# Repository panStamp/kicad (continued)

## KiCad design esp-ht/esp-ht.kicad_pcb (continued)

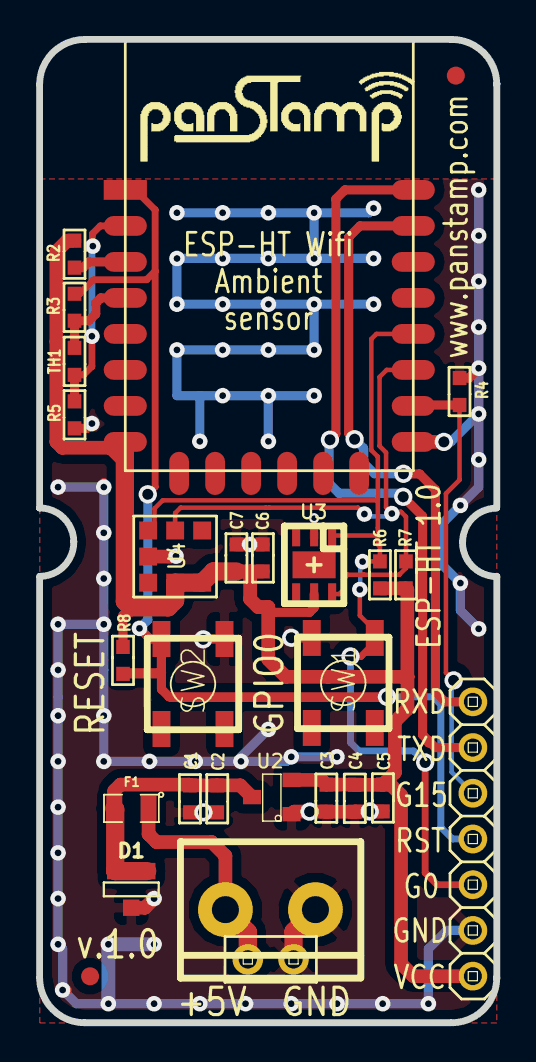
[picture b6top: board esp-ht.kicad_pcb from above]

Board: 2 copper layers, 25.4 x 54.6 mm, 28 parts (0 on the bottom side), 13 nets.

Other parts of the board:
fiducial: VAL**; fiducial
fiducial#2: VAL**; fiducial

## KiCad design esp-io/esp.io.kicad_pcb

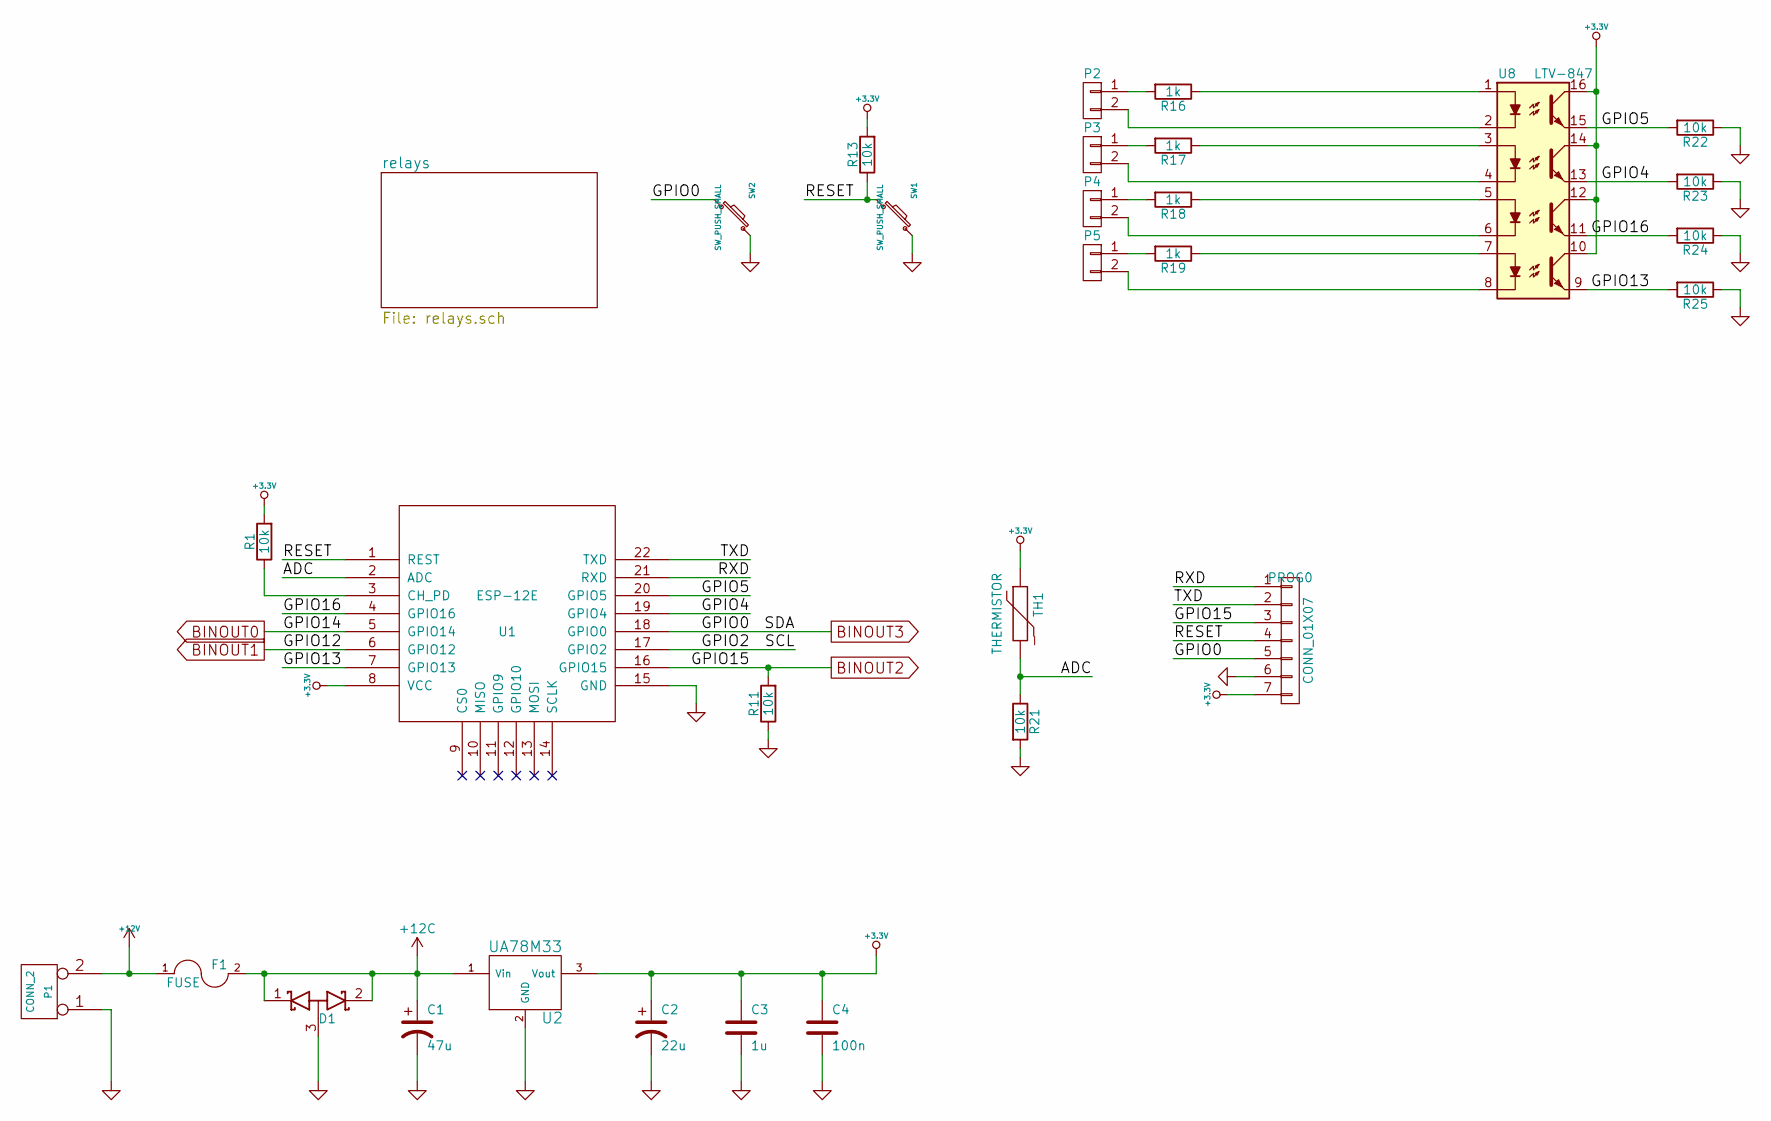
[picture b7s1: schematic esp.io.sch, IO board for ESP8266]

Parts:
C1: 47u; SMDCPOL_6.3
C2: 22u; SMDCPOL_5
C3: 1u; SM0603S
C4: 100n; SM0603S
D1: D_Schottky_x2_ACom_KKA; SOT23
F1: FUSE; SM1206
P1: CONN_2; terminal_block_5mm_2P
P2, P3, P4, P5: CONN_01X02; terminal_block_5mm_2P
PROG0: CONN_01X07; pinhead-1X07
R1, R11, R13, R21, R22, R23, R24, R25: 10k; SM0603S
R16, R17, R18, R19: 1k; SM0603S
SW1, SW2: SW_PUSH_SMALL; switch-tact-noah
TH1: THERMISTOR; SM0603S
U1: ESP-12E
U2: UA78M33; SOT223
U8: LTV-847; DIP16_SMD

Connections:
+3.3V: C2.1, C3.1, C4.1, PROG0.7, R1.2, R13.2, TH1.1, U1.8 (VCC), U2.3 (Vout), U8.10, U8.12, U8.14, U8.16
+12C: C1.1, D1.1 (K), D1.2 (K), F1.2, U2.1 (Vin); also elsewhere on the board
+12V: F1.1, P1.2 (PM)
/ADC: R21.1, TH1.2, U1.2 (ADC)
/GPIO2: U1.17 (GPIO2)
/GPIO4: R23.2, U1.19 (GPIO4), U8.13
/GPIO5: R22.2, U1.20 (GPIO5), U8.15
/GPIO13: R25.2, U1.7 (GPIO13), U8.9
/GPIO16: R24.2, U1.4 (GPIO16), U8.11
/RESET: PROG0.4, R13.1, SW1.2, U1.1 (REST)
/RXD: PROG0.1, U1.21 (RXD)
/TXD: PROG0.2, U1.22 (TXD)
BINOUT0: U1.5 (GPIO14); also elsewhere on the board
BINOUT1: U1.6 (GPIO12); also elsewhere on the board
BINOUT2: PROG0.3, R11.2, U1.16 (GPIO15); also elsewhere on the board
BINOUT3: PROG0.5, SW2.2, U1.18 (GPIO0); also elsewhere on the board
GND: C1.2, C2.2, C3.2, C4.2, D1.3 (A), P1.1, PROG0.6, R11.1, R21.2, R22.1, R23.1, R24.1, R25.1, SW1.1, SW2.1, U1.15 (GND), U2.2 (GND), U2.4; also elsewhere on the board
unnamed: P2.1, R16.2
unnamed: P2.2, U8.2
unnamed: P3.1, R17.2
unnamed: P3.2, U8.4
unnamed: P4.1, R18.2
unnamed: P4.2, U8.6
unnamed: P5.1, R19.2
unnamed: P5.2, U8.8
unnamed: R1.1, U1.3 (CH_PD)
unnamed: R16.1, U8.1
unnamed: R17.1, U8.3
unnamed: R18.1, U8.5
unnamed: R19.1, U8.7

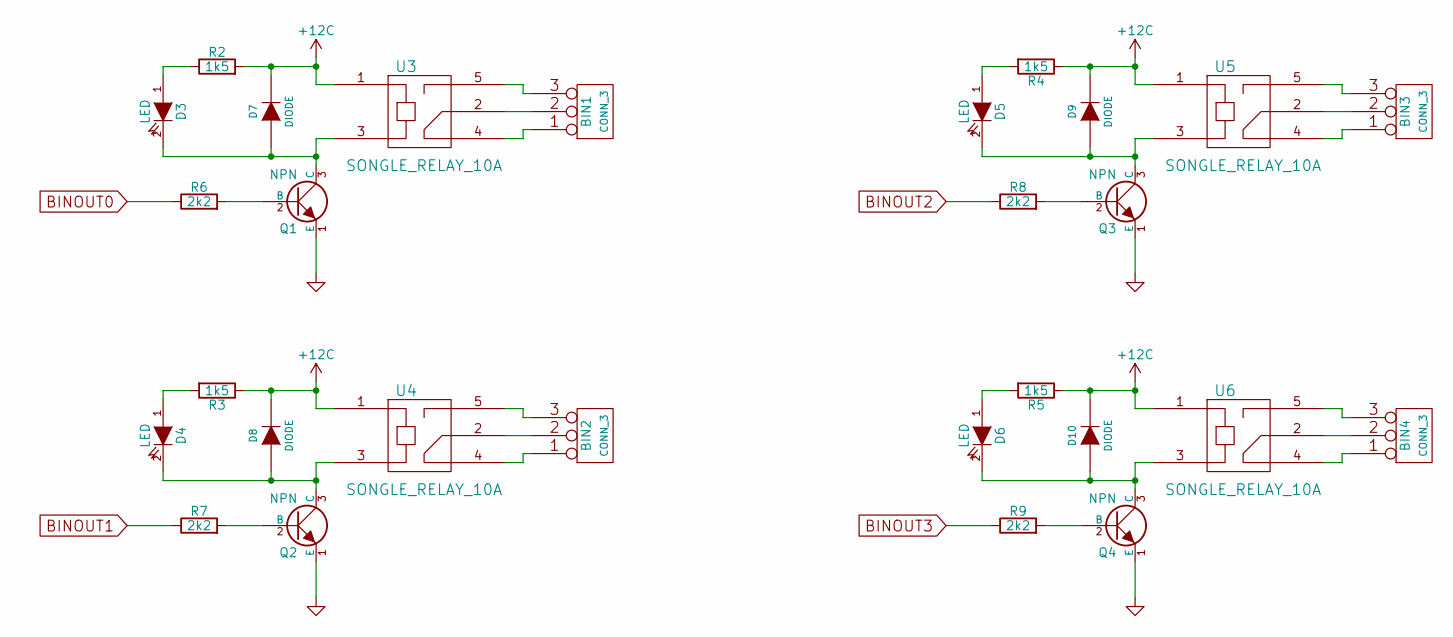
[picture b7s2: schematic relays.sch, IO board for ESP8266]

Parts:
BIN1, BIN2, BIN3, BIN4: CONN_3; terminal_block_5mm_3P
D3, D4, D5, D6: LED; SM0603S_POL
D7, D8, D9, D10: DIODE; SOD323
Q1, Q2, Q3, Q4: NPN; SOT23EBC
R2, R3, R4, R5: 1k5; SM0603S
R6, R7, R8, R9: 2k2; SM0603S
U3, U4, U5, U6: SONGLE_RELAY_10A

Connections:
+12C: D7.2 (K), D8.2 (K), D9.2 (K), D10.2 (K), R2.2, R3.1, R4.1, R5.1, U3.1, U4.1, U5.1, U6.1; also elsewhere on the board
BINOUT0: R6.1; also elsewhere on the board
BINOUT1: R7.1; also elsewhere on the board
BINOUT2: R8.1; also elsewhere on the board
BINOUT3: R9.1; also elsewhere on the board
GND: Q1.1 (E), Q2.1 (E), Q3.1 (E), Q4.1 (E); also elsewhere on the board
unnamed: BIN1.1, U3.4
unnamed: BIN1.2 (PM), U3.2
unnamed: BIN1.3, U3.5
unnamed: BIN2.1, U4.4
unnamed: BIN2.2 (PM), U4.2
unnamed: BIN2.3, U4.5
unnamed: BIN3.1, U5.4
unnamed: BIN3.2 (PM), U5.2
unnamed: BIN3.3, U5.5
unnamed: BIN4.1, U6.4
unnamed: BIN4.2 (PM), U6.2
unnamed: BIN4.3, U6.5
unnamed: D3.1 (A), R2.1
unnamed: D3.2 (K), D7.1 (A), Q1.3 (C), U3.3
unnamed: D4.1 (A), R3.2
unnamed: D4.2 (K), D8.1 (A), Q2.3 (C), U4.3
unnamed: D5.1 (A), R4.2
unnamed: D5.2 (K), D9.1 (A), Q3.3 (C), U5.3
unnamed: D6.1 (A), R5.2
unnamed: D6.2 (K), D10.1 (A), Q4.3 (C), U6.3
unnamed: Q1.2 (B), R6.2
unnamed: Q2.2 (B), R7.2
unnamed: Q3.2 (B), R8.2
unnamed: Q4.2 (B), R9.2

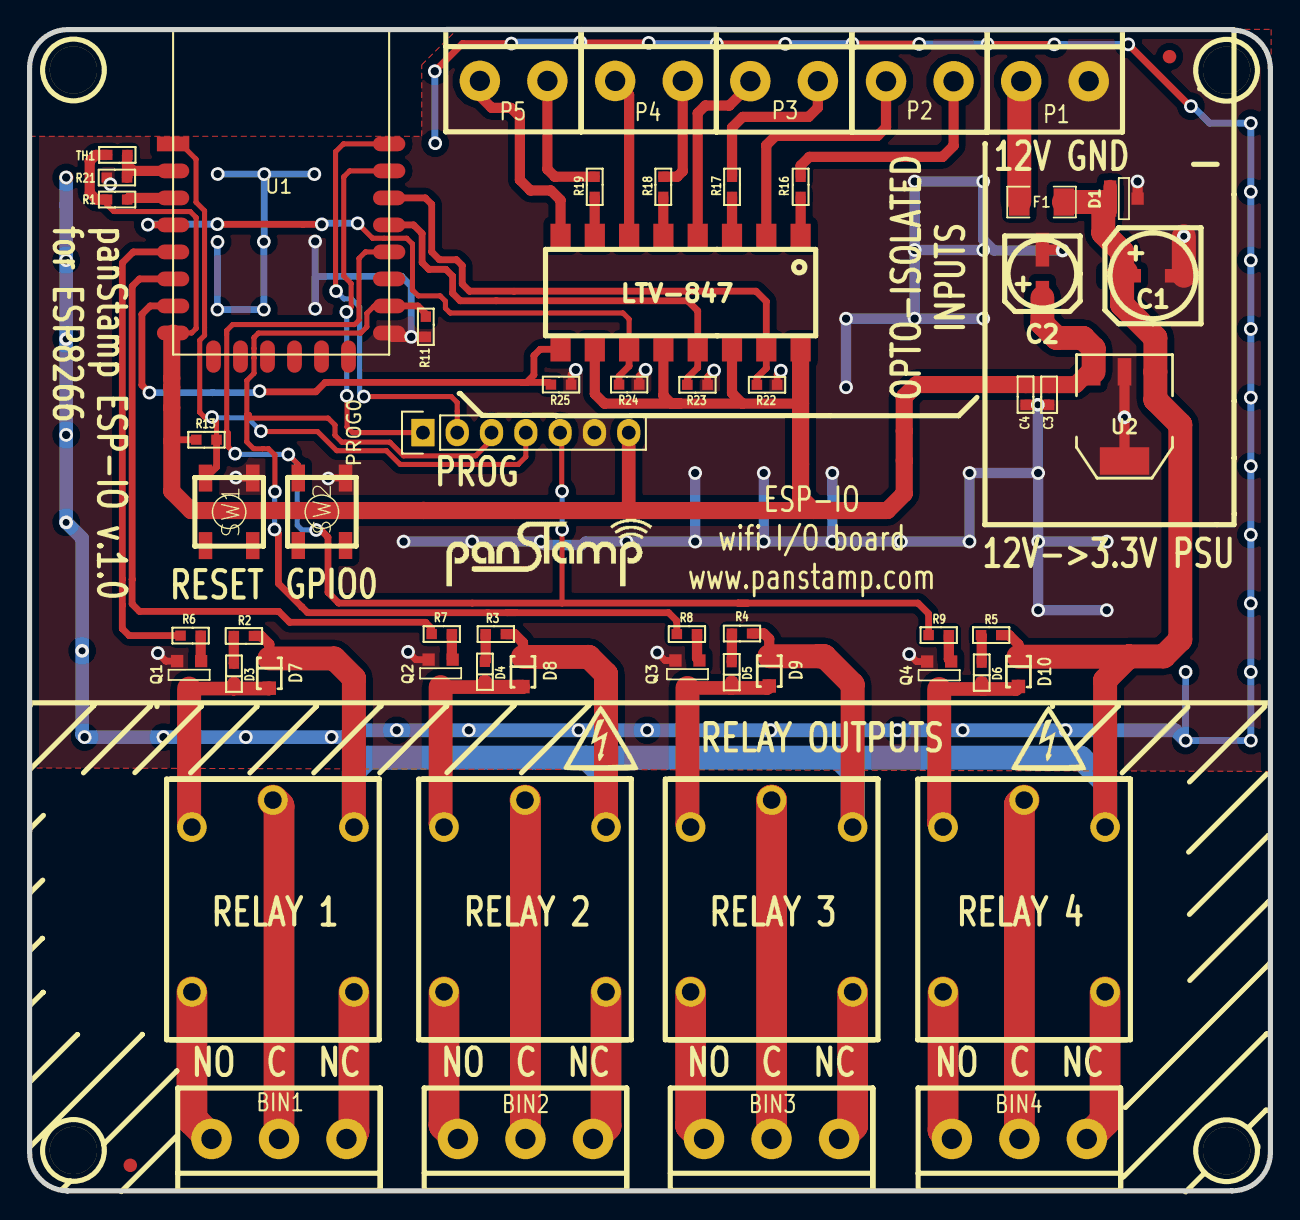
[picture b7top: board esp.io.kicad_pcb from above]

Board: 2 copper layers, 91.9 x 86.0 mm, 64 parts (0 on the bottom side), 53 nets.

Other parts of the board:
1PIN, 1PIN#2, 1PIN#3, 1PIN#4: P***; 1pin
fiducial: VAL**; fiducial
fiducial#2: VAL**; fiducial
